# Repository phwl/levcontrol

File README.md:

# Optical levitation project

 * **pylqg_project**
   - A good starting point is [pylqg_project/notebooks/levitated_optomechanics_LQG_1d.ipynb](https://github.com/phwl/levcontrol/blob/main/pylqg_project/notebooks/levitated_optomechanics_LQG_1d.ipynb) which is a tutorial explaining the idea in 1D.
   - The high-level DAC board design is in [pylqg_project/notebooks/AD3552R_four_channel_DAC_circuit_design_tutorial.ipynb](https://github.com/phwl/levcontrol/blob/main/pylqg_project/notebooks/AD3552R_four_channel_DAC_circuit_design_tutorial.ipynb) and the details in [ad3552r_dac/docs/AD3552R_DAC_Mezzanine_Design_Manual.docx](https://github.com/phwl/levcontrol/blob/main/ad3552r_dac/docs/AD3552R_DAC_Mezzanine_Design_Manual.docx)
   - A notebook to reproduce the paper is here [pylqg_project/notebooks/pylqg_tutorial.ipynb](https://github.com/phwl/levcontrol/blob/main/pylqg_project/notebooks/pylqg_tutorial.ipynb)
 * **LQGcontroller** - repository containing the code and artifacts accompanying the article: "FPGA-based LQG controller and hardware-in-the-loop simulator implementation for nanomechanical systems"

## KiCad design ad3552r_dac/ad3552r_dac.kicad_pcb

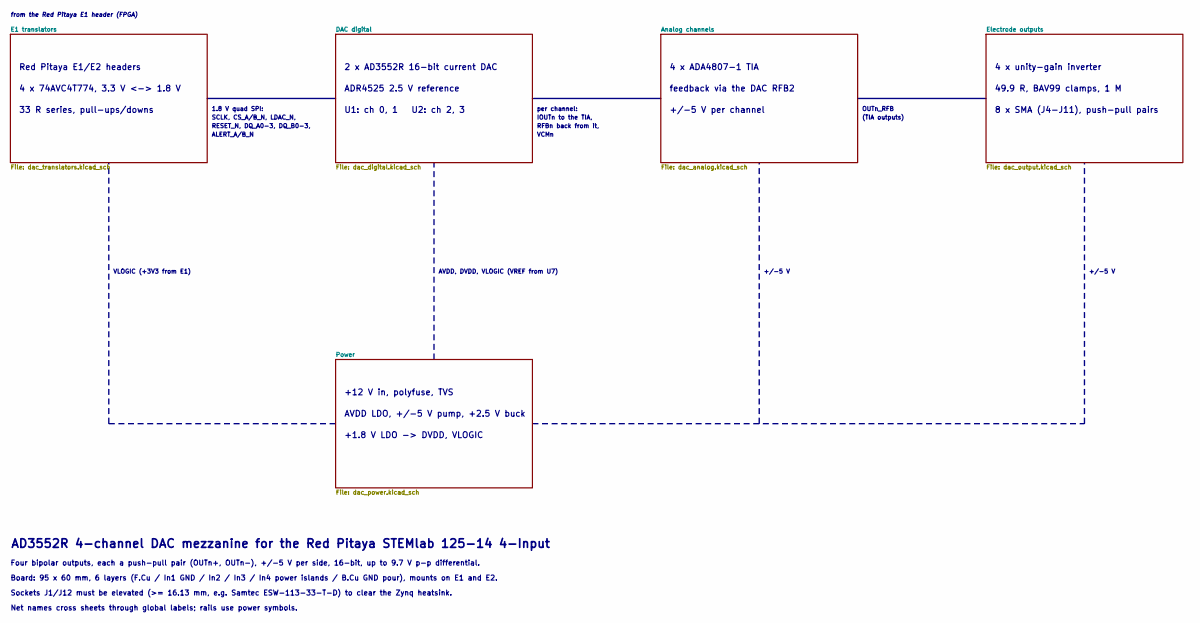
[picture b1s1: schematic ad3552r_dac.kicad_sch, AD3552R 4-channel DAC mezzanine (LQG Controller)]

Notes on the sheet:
Red Pitaya E1/E2 headers
+1.8 V LDO -> DVDD, VLOGIC
Board: 95 x 60 mm, 6 layers (F.Cu / In1 GND / In2 / In3 / In4 power islands / B.Cu GND pour), mounts on E1 and E2.
+12 V in, polyfuse, TVS
RESET_N, DQ_A0-3, DQ_B0-3,
2 x AD3552R 16-bit current DAC
U1: ch 0, 1 U2: ch 2, 3
4 x unity-gain inverter
ALERT_A/B_N
AVDD LDO, +/-5 V pump, +2.5 V buck
AVDD, DVDD, VLOGIC (VREF from U7)
+/-5 V
OUTn_RFB
+/-5 V per channel
per channel:
(TIA outputs)
from the Red Pitaya E1 header (FPGA)
RFBn back from it,
IOUTn to the TIA,
4 x ADA4807-1 TIA
4 x 74AVC4T774, 3.3 V <-> 1.8 V
Sockets J1/J12 must be elevated (>= 16.13 mm, e.g. Samtec ESW-113-33-T-D) to clear the Zynq heatsink.
8 x SMA (J4-J11), push-pull pairs
33 R series, pull-ups/downs
49.9 R, BAV99 clamps, 1 M
SCLK, CS_A/B_N, LDAC_N,
VLOGIC (+3V3 from E1)
1.8 V quad SPI:
AD3552R 4-channel DAC mezzanine for the Red Pitaya STEMlab 125-14 4-Input
Four bipolar outputs, each a push-pull pair (OUTn+, OUTn-), +/-5 V per side, 16-bit, up to 9.7 V p-p differential.
ADR4525 2.5 V reference
VCMn
Net names cross sheets through global labels; rails use power symbols.
feedback via the DAC RFB2

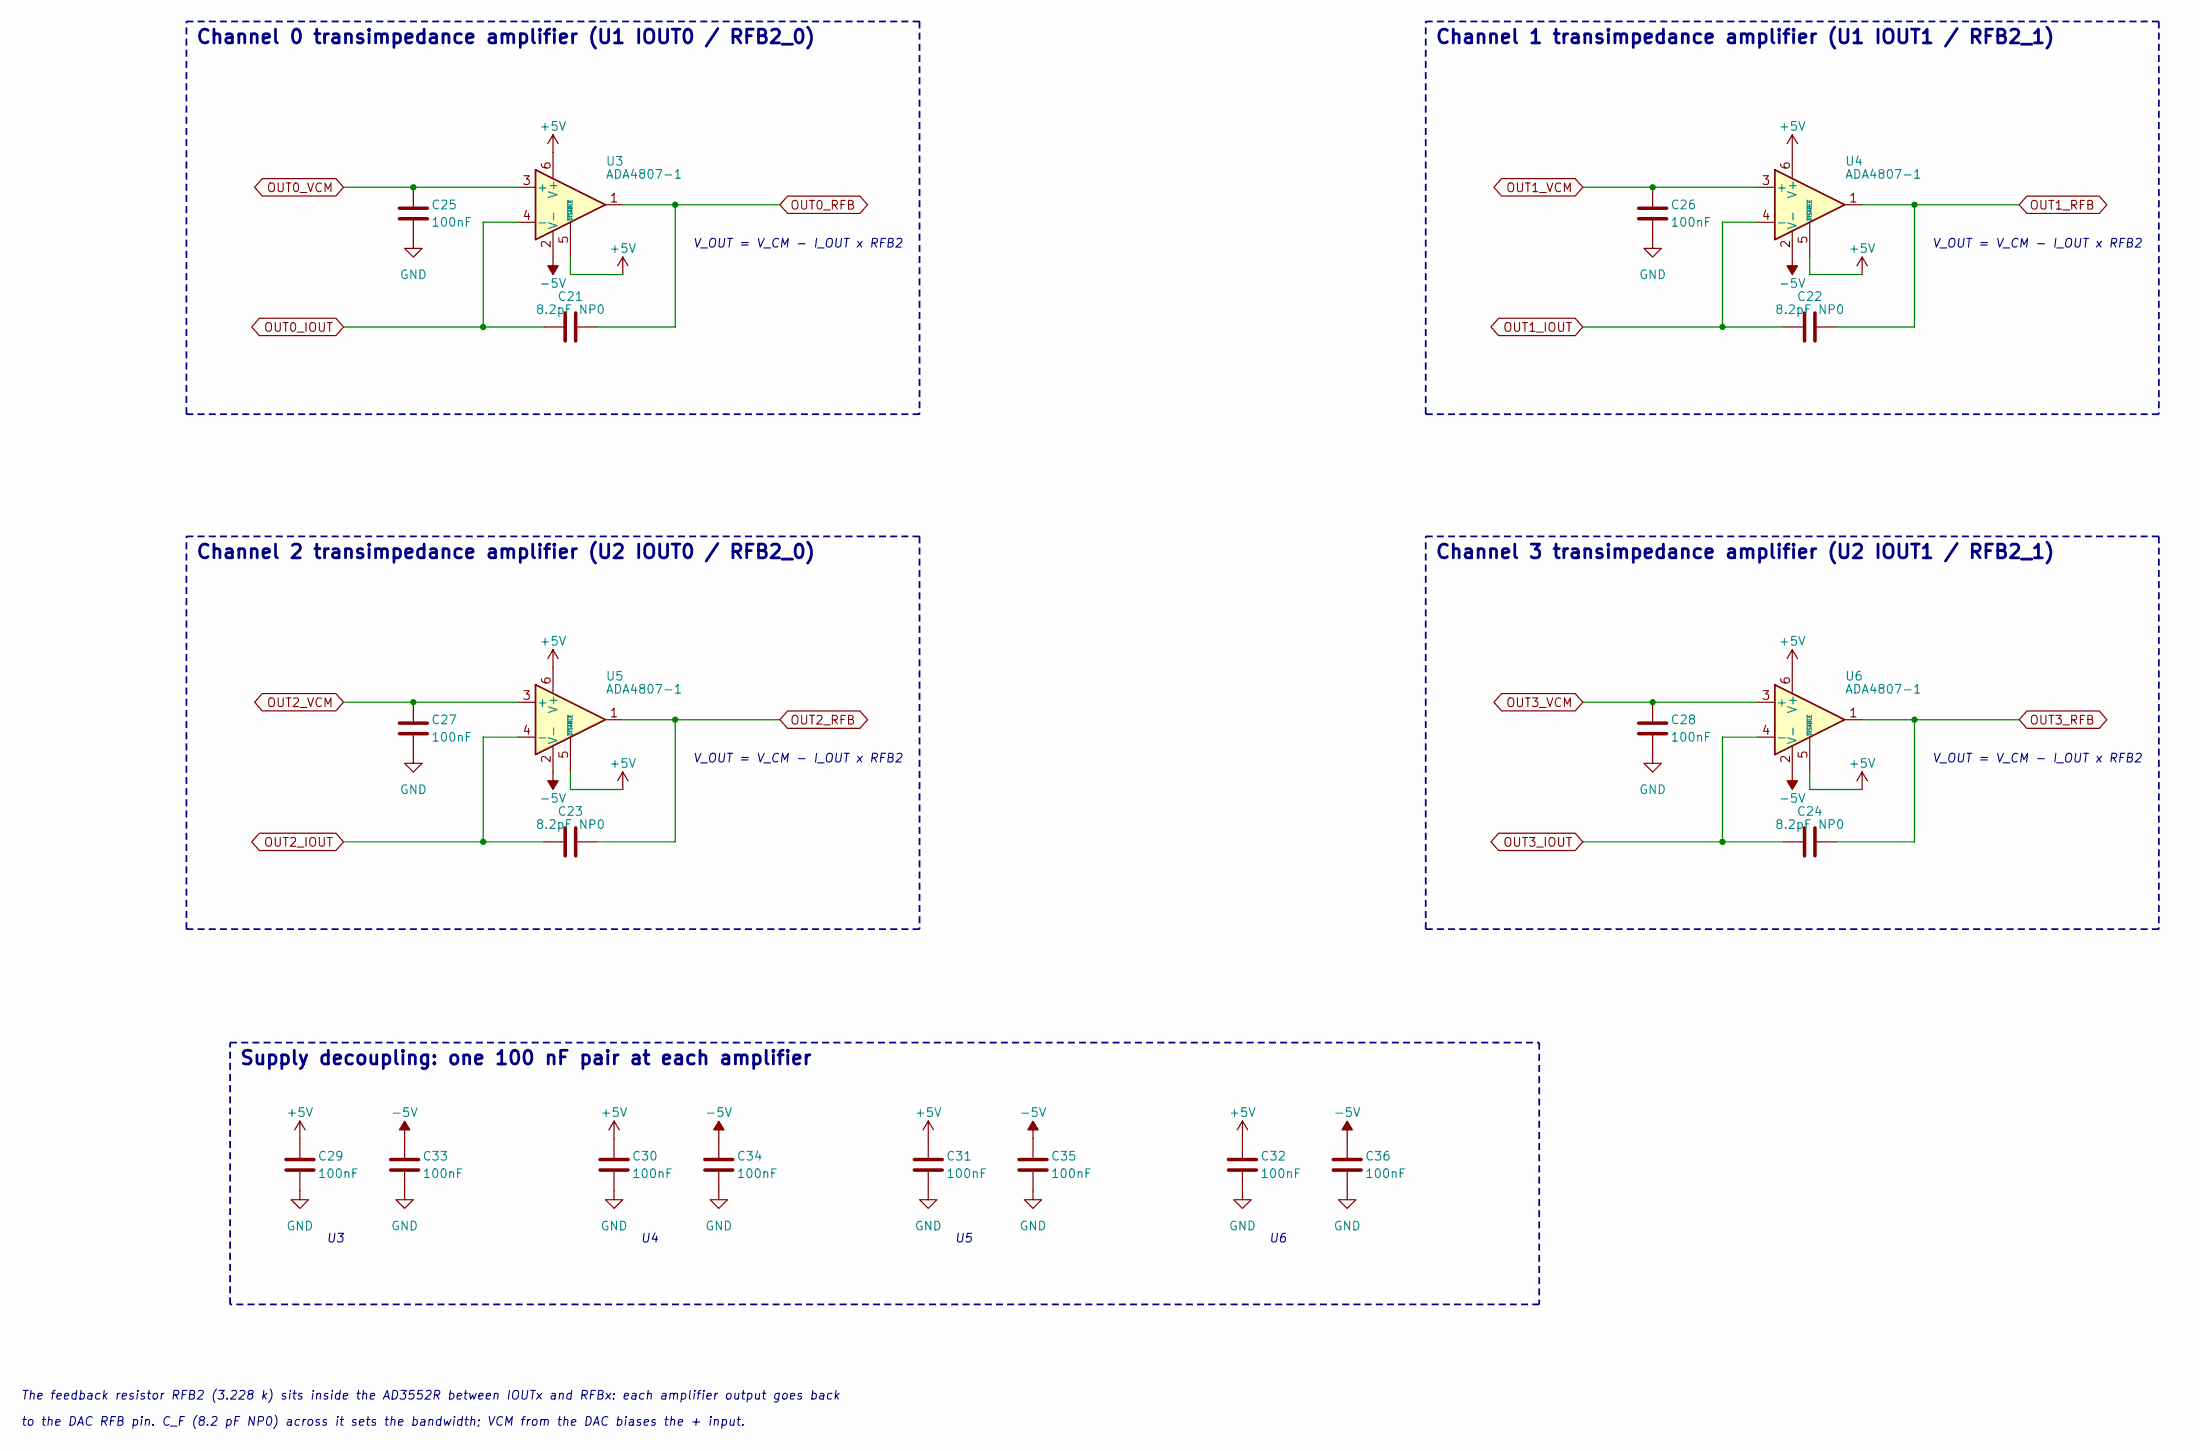
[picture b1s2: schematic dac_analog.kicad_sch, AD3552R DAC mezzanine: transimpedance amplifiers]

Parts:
C21, C22, C23, C24: 8.2pF NP0; C_0402_1005Metric; MPN 0402CG8R2C500NT; LCSC C1579
C25, C26, C27, C28, C29, C30, C31, C32, C33, C34, C35, C36: 100nF; C_0402_1005Metric; MPN CL05B104KO5NNNC; LCSC C1525
U3, U4, U5, U6: ADA4807-1; SOT-23-6; MPN ADA4807-1ARJZ-R7; LCSC C2058411

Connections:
+5V: C29.1, C30.1, C31.1, C32.1, U3.5 (~DISABLE), U3.6 (V+), U4.5 (~DISABLE), U4.6 (V+), U5.5 (~DISABLE), U5.6 (V+), U6.5 (~DISABLE), U6.6 (V+); also elsewhere on the board
-5V: C33.2, C34.2, C35.2, C36.2, U3.2 (V-), U4.2 (V-), U5.2 (V-), U6.2 (V-); also elsewhere on the board
GND: C25.2, C26.2, C27.2, C28.2, C29.2, C30.2, C31.2, C32.2, C33.1, C34.1, C35.1, C36.1; also elsewhere on the board
OUT0_IOUT: C21.1, U3.4 (-); also elsewhere on the board
OUT0_RFB: C21.2, U3.1; also elsewhere on the board
OUT0_VCM: C25.1, U3.3 (+); also elsewhere on the board
OUT1_IOUT: C22.1, U4.4 (-); also elsewhere on the board
OUT1_RFB: C22.2, U4.1; also elsewhere on the board
OUT1_VCM: C26.1, U4.3 (+); also elsewhere on the board
OUT2_IOUT: C23.1, U5.4 (-); also elsewhere on the board
OUT2_RFB: C23.2, U5.1; also elsewhere on the board
OUT2_VCM: C27.1, U5.3 (+); also elsewhere on the board
OUT3_IOUT: C24.1, U6.4 (-); also elsewhere on the board
OUT3_RFB: C24.2, U6.1; also elsewhere on the board
OUT3_VCM: C28.1, U6.3 (+); also elsewhere on the board

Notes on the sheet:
Supply decoupling: one 100 nF pair at each amplifier
Channel 3 transimpedance amplifier (U2 IOUT1 / RFB2_1)
V_OUT = V_CM - I_OUT x RFB2
Channel 0 transimpedance amplifier (U1 IOUT0 / RFB2_0)
Channel 2 transimpedance amplifier (U2 IOUT0 / RFB2_0)
Channel 1 transimpedance amplifier (U1 IOUT1 / RFB2_1)
to the DAC RFB pin. C_F (8.2 pF NP0) across it sets the bandwidth; VCM from the DAC biases the + input.
The feedback resistor RFB2 (3.228 k) sits inside the AD3552R between IOUTx and RFBx: each amplifier output goes back

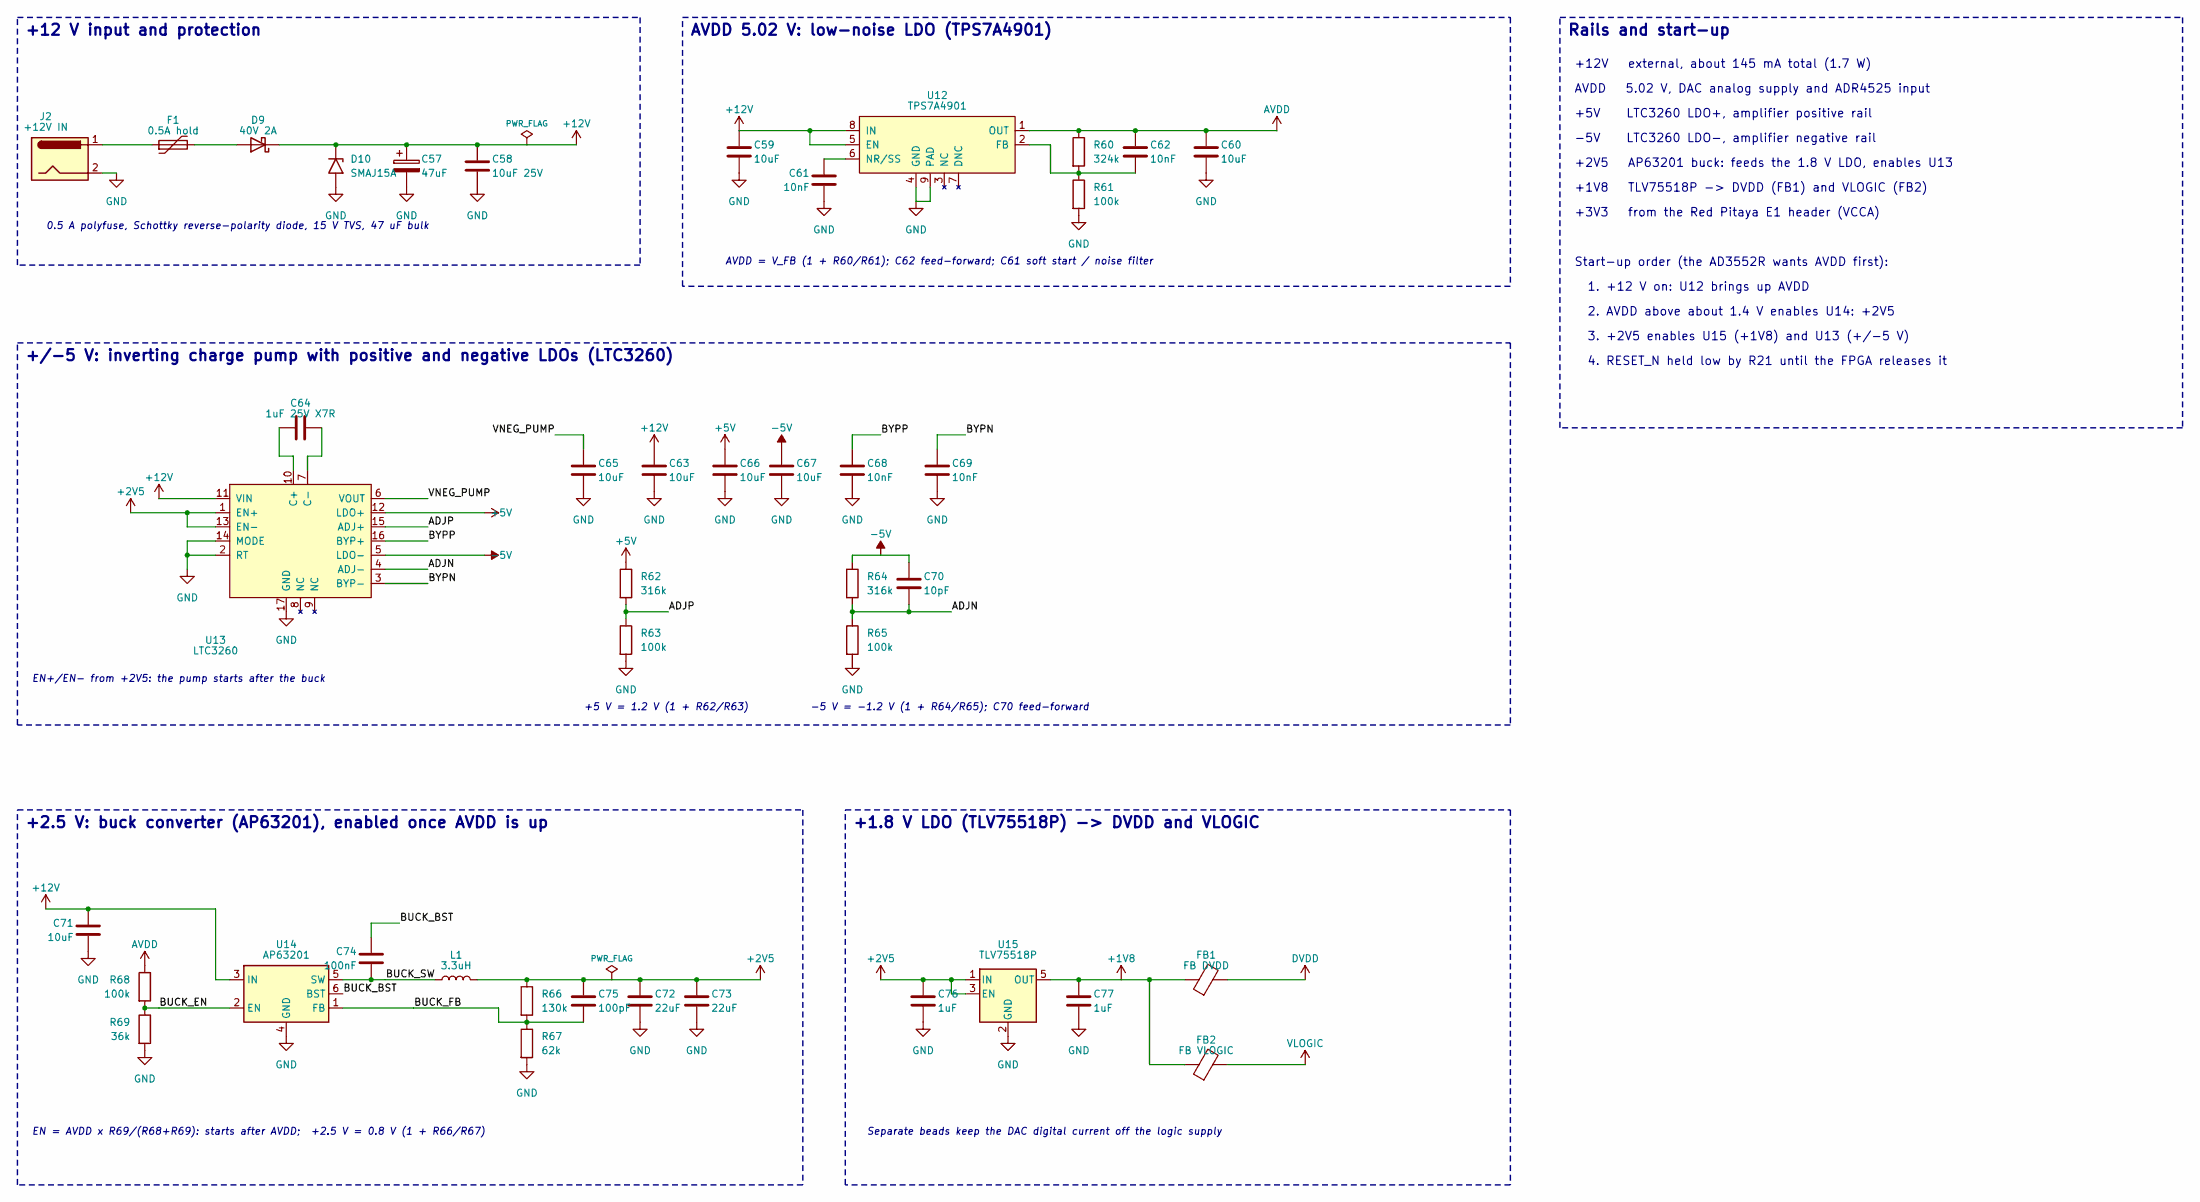
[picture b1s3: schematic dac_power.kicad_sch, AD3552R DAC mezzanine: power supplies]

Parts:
C57: 47uF; CP_Elec_6.3x5.4; MPN FVH025ADA470M0654; LCSC C7469965
C58: 10uF 25V; C_0805_2012Metric; MPN CGA0805X7R106K250MT; LCSC C6119932
C59, C60, C63, C65, C66, C67, C71: 10uF; C_0805_2012Metric; MPN CGA0805X7R106K250MT; LCSC C6119932
C61, C62, C68, C69: 10nF; C_0402_1005Metric; MPN CL05B103KB5NNNC; LCSC C15195
C64: 1uF 25V X7R; C_0603_1608Metric; MPN CC0603KRX7R8BB105; LCSC C106858
C70: 10pF; C_0402_1005Metric; MPN 0402CG100J500NT; LCSC C1545
C72, C73: 22uF; C_0805_2012Metric; MPN CL21A226MAQNNNE; LCSC C45783
C74: 100nF; C_0402_1005Metric; MPN CL05B104KO5NNNC; LCSC C1525
C75: 100pF; C_0402_1005Metric; MPN 0402CG101J500NT; LCSC C1546
C76, C77: 1uF; C_0402_1005Metric; MPN CL05A105KA5NQNC; LCSC C52923
D9: 40V 2A; D_SMA; MPN SS24; LCSC C50645
D10: SMAJ15A; D_SMA; MPN SMAJ15A/TR13; LCSC C86819
F1: 0.5A hold; Fuse_1206_3216Metric; MPN SMD1206P050TF/24; LCSC C492011
FB1: FB DVDD; L_0603_1608Metric; MPN BLM18PG221SN1D; LCSC C80165
FB2: FB VLOGIC; L_0603_1608Metric; MPN BLM18PG221SN1D; LCSC C80165
J2: +12V IN; BarrelJack_Horizontal; MPN PJ-102AH; LCSC C3096093
L1: 3.3uH; L_Taiyo-Yuden_NR-50xx; MPN SWPA5040S3R3NT; LCSC C305173
R60: 324k; R_0402_1005Metric; MPN 0402WGF3243TCE; LCSC C113480
R61, R63, R65, R68: 100k; R_0402_1005Metric; MPN 0402WGF1003TCE; LCSC C25741
R62, R64: 316k; R_0402_1005Metric; MPN 0402WGF3163TCE; LCSC C25777
R66: 130k; R_0402_1005Metric; MPN 0402WGF1303TCE; LCSC C52929
R67: 62k; R_0402_1005Metric; MPN 0402WGF6202TCE; LCSC C37825
R69: 36k; R_0402_1005Metric; MPN 0402WGF3602TCE; LCSC C43676
U12: TPS7A4901; HVSSOP-8-1EP_3x3mm_P0.65mm_EP1.57x1.89mm; MPN TPS7A4901DGNR; LCSC C16430
U13: LTC3260; MSOP-16-1EP_3x4mm_P0.5mm_EP1.65x2.85mm; MPN LTC3260EMSE#TRPBF; LCSC C684387
U14: AP63201; TSOT-23-6; MPN AP63201WU-7; LCSC C2071044
U15: TLV75518P; SOT-23-5; MPN TLV75518PDBVR; LCSC C2877863

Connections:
+1V8: C77.1, FB1.1, FB2.1, U15.5 (OUT)
+2V5: C72.1, C73.1, C75.1, C76.1, L1.2, R66.1, U13.1 (EN+), U13.13 (EN-), U15.1 (IN), U15.3 (EN)
+5V: C66.1, R62.1, U13.12 (LDO+); also elsewhere on the board
+12V: C57.1, C58.1, C59.1, C63.1, C71.1, D9.1 (K), D10.1 (A1), U12.5 (EN), U12.8 (IN), U13.11 (VIN), U14.3 (IN)
-5V: C67.1, C70.1, R64.1, U13.5 (LDO-); also elsewhere on the board
/Power/ADJN: C70.2, R64.2, R65.1, U13.4 (ADJ-)
/Power/ADJP: R62.2, R63.1, U13.15 (ADJ+)
/Power/BUCK_BST: C74.2, U14.6 (BST)
/Power/BUCK_EN: R68.2, R69.1, U14.2 (EN)
/Power/BUCK_FB: C75.2, R66.2, R67.1, U14.1 (FB)
/Power/BUCK_SW: C74.1, L1.1, U14.5 (SW)
/Power/BYPN: C69.1, U13.3 (BYP-)
/Power/BYPP: C68.1, U13.16 (BYP+)
/Power/VNEG_PUMP: C65.1, U13.6 (VOUT)
AVDD: C60.1, C62.1, R60.1, R68.1, U12.1 (OUT); also elsewhere on the board
DVDD: FB1.2; also elsewhere on the board
GND: C57.2, C58.2, C59.2, C60.2, C61.2, C63.2, C65.2, C66.2, C67.2, C68.2, C69.2, C71.2, C72.2, C73.2, C76.2, C77.2, D10.2 (A2), J2.2, R61.2, R63.2, R65.2, R67.2, R69.2, U12.4 (GND), U12.9 (PAD), U13.2 (RT), U13.14 (MODE), U13.17 (GND), U14.4 (GND), U15.2 (GND); also elsewhere on the board
unnamed: D9.2 (A), F1.2
unnamed: F1.1, J2.1
unnamed: C62.2, R60.2, R61.1, U12.2 (FB)
unnamed: C61.1, U12.6 (NR/SS)
unnamed: C64.1, U13.10 (C+)
unnamed: C64.2, U13.7 (C-)
VLOGIC: FB2.2; also elsewhere on the board

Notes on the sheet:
Start-up order (the AD3552R wants AVDD first):
3. +2V5 enables U15 (+1V8) and U13 (+/-5 V)
+5 V = 1.2 V (1 + R62/R63)
4. RESET_N held low by R21 until the FPGA releases it
+3V3 from the Red Pitaya E1 header (VCCA)
-5 V = -1.2 V (1 + R64/R65); C70 feed-forward
-5V LTC3260 LDO-, amplifier negative rail
+2V5 AP63201 buck: feeds the 1.8 V LDO, enables U13
+12V external, about 145 mA total (1.7 W)
+12 V input and protection
AVDD = V_FB (1 + R60/R61); C62 feed-forward; C61 soft start / noise filter
+5V LTC3260 LDO+, amplifier positive rail
AVDD 5.02 V, DAC analog supply and ADR4525 input
Rails and start-up
+1.8 V LDO (TLV75518P) -> DVDD and VLOGIC
1. +12 V on: U12 brings up AVDD
EN = AVDD x R69/(R68+R69): starts after AVDD; +2.5 V = 0.8 V (1 + R66/R67)
+1V8 TLV75518P -> DVDD (FB1) and VLOGIC (FB2)
EN+/EN- from +2V5: the pump starts after the buck
Separate beads keep the DAC digital current off the logic supply
0.5 A polyfuse, Schottky reverse-polarity diode, 15 V TVS, 47 uF bulk
+/-5 V: inverting charge pump with positive and negative LDOs (LTC3260)
+2.5 V: buck converter (AP63201), enabled once AVDD is up
2. AVDD above about 1.4 V enables U14: +2V5
AVDD 5.02 V: low-noise LDO (TPS7A4901)

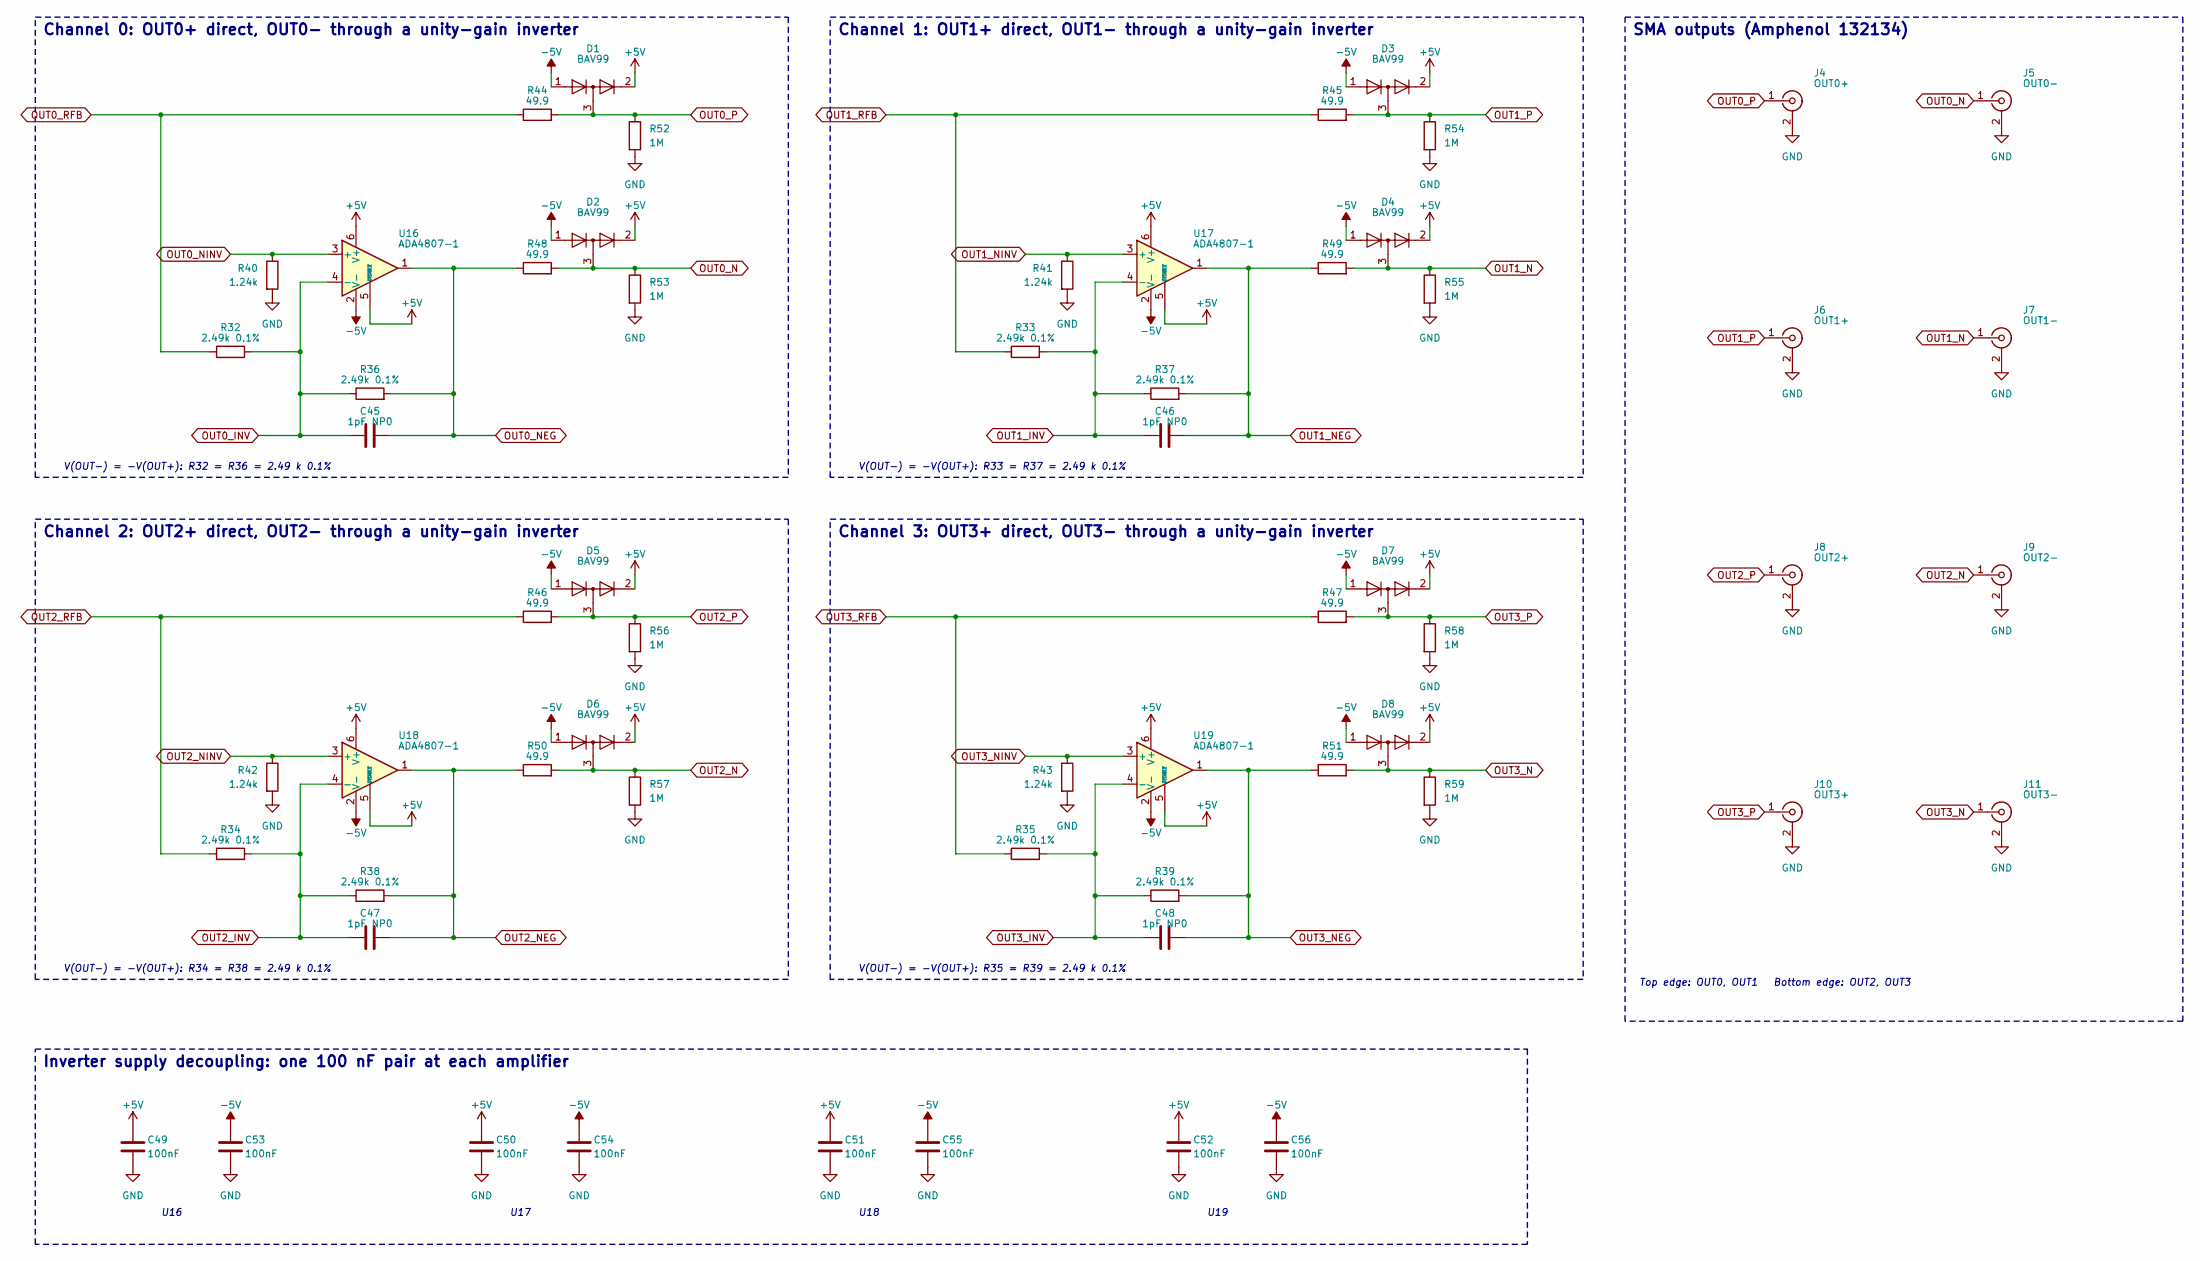
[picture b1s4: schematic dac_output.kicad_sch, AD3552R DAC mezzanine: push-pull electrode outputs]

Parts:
C45, C46, C47, C48: 1pF NP0; C_0402_1005Metric; MPN 0402CG1R0C500NT; LCSC C1550
C49, C50, C51, C52, C53, C54, C55, C56: 100nF; C_0402_1005Metric; MPN CL05B104KO5NNNC; LCSC C1525
D1, D2, D3, D4, D5, D6, D7, D8: BAV99; SOT-23; MPN BAV99,215; LCSC C2500
J4: OUT0+; SMA_Amphenol_132134_Vertical; MPN 132134; LCSC C3174425
J5: OUT0-; SMA_Amphenol_132134_Vertical; MPN 132134; LCSC C3174425
J6: OUT1+; SMA_Amphenol_132134_Vertical; MPN 132134; LCSC C3174425
J7: OUT1-; SMA_Amphenol_132134_Vertical; MPN 132134; LCSC C3174425
J8: OUT2+; SMA_Amphenol_132134_Vertical; MPN 132134; LCSC C3174425
J9: OUT2-; SMA_Amphenol_132134_Vertical; MPN 132134; LCSC C3174425
J10: OUT3+; SMA_Amphenol_132134_Vertical; MPN 132134; LCSC C3174425
J11: OUT3-; SMA_Amphenol_132134_Vertical; MPN 132134; LCSC C3174425
R32, R33, R34, R35, R36, R37, R38, R39: 2.49k 0.1%; R_0603_1608Metric; MPN RT0603BRD072K49L; LCSC C861299
R40, R41, R42, R43: 1.24k; R_0402_1005Metric; MPN 0402WGF1241TCE; LCSC C25864
R44, R45, R46, R47, R48, R49, R50, R51: 49.9; R_0402_1005Metric; MPN 0402WGF499JTCE; LCSC C25120
R52, R53, R54, R55, R56, R57, R58, R59: 1M; R_0402_1005Metric; MPN 0402WGF1004TCE; LCSC C26083
U16, U17, U18, U19: ADA4807-1; SOT-23-6; MPN ADA4807-1ARJZ-R7; LCSC C2058411

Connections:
+5V: C49.1, C50.1, C51.1, C52.1, D1.2 (A), D2.2 (A), D3.2 (A), D4.2 (A), D5.2 (A), D6.2 (A), D7.2 (A), D8.2 (A), U16.5 (~DISABLE), U16.6 (V+), U17.5 (~DISABLE), U17.6 (V+), U18.5 (~DISABLE), U18.6 (V+), U19.5 (~DISABLE), U19.6 (V+); also elsewhere on the board
-5V: C53.2, C54.2, C55.2, C56.2, D1.1 (K), D2.1 (K), D3.1 (K), D4.1 (K), D5.1 (K), D6.1 (K), D7.1 (K), D8.1 (K), U16.2 (V-), U17.2 (V-), U18.2 (V-), U19.2 (V-); also elsewhere on the board
GND: C49.2, C50.2, C51.2, C52.2, C53.1, C54.1, C55.1, C56.1, J4.2 (Ext), J5.2 (Ext), J6.2 (Ext), J7.2 (Ext), J8.2 (Ext), J9.2 (Ext), J10.2 (Ext), J11.2 (Ext), R40.2, R41.2, R42.2, R43.2, R52.2, R53.2, R54.2, R55.2, R56.2, R57.2, R58.2, R59.2; also elsewhere on the board
OUT0_INV: C45.1, R32.2, R36.1, U16.4 (-)
OUT0_N: D2.3 (K), J5.1 (In), R48.2, R53.1
OUT0_NEG: C45.2, R36.2, R48.1, U16.1
OUT0_NINV: R40.1, U16.3 (+)
OUT0_P: D1.3 (K), J4.1 (In), R44.2, R52.1
OUT0_RFB: R32.1, R44.1; also elsewhere on the board
OUT1_INV: C46.1, R33.2, R37.1, U17.4 (-)
OUT1_N: D4.3 (K), J7.1 (In), R49.2, R55.1
OUT1_NEG: C46.2, R37.2, R49.1, U17.1
OUT1_NINV: R41.1, U17.3 (+)
OUT1_P: D3.3 (K), J6.1 (In), R45.2, R54.1
OUT1_RFB: R33.1, R45.1; also elsewhere on the board
OUT2_INV: C47.1, R34.2, R38.1, U18.4 (-)
OUT2_N: D6.3 (K), J9.1 (In), R50.2, R57.1
OUT2_NEG: C47.2, R38.2, R50.1, U18.1
OUT2_NINV: R42.1, U18.3 (+)
OUT2_P: D5.3 (K), J8.1 (In), R46.2, R56.1
OUT2_RFB: R34.1, R46.1; also elsewhere on the board
OUT3_INV: C48.1, R35.2, R39.1, U19.4 (-)
OUT3_N: D8.3 (K), J11.1 (In), R51.2, R59.1
OUT3_NEG: C48.2, R39.2, R51.1, U19.1
OUT3_NINV: R43.1, U19.3 (+)
OUT3_P: D7.3 (K), J10.1 (In), R47.2, R58.1
OUT3_RFB: R35.1, R47.1; also elsewhere on the board

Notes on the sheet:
Channel 2: OUT2+ direct, OUT2- through a unity-gain inverter
Channel 1: OUT1+ direct, OUT1- through a unity-gain inverter
Top edge: OUT0, OUT1 Bottom edge: OUT2, OUT3
U17
U16
Inverter supply decoupling: one 100 nF pair at each amplifier
SMA outputs (Amphenol 132134)
U19
V(OUT-) = -V(OUT+): R34 = R38 = 2.49 k 0.1%
V(OUT-) = -V(OUT+): R33 = R37 = 2.49 k 0.1%
Channel 3: OUT3+ direct, OUT3- through a unity-gain inverter
U18
Channel 0: OUT0+ direct, OUT0- through a unity-gain inverter
V(OUT-) = -V(OUT+): R35 = R39 = 2.49 k 0.1%
V(OUT-) = -V(OUT+): R32 = R36 = 2.49 k 0.1%

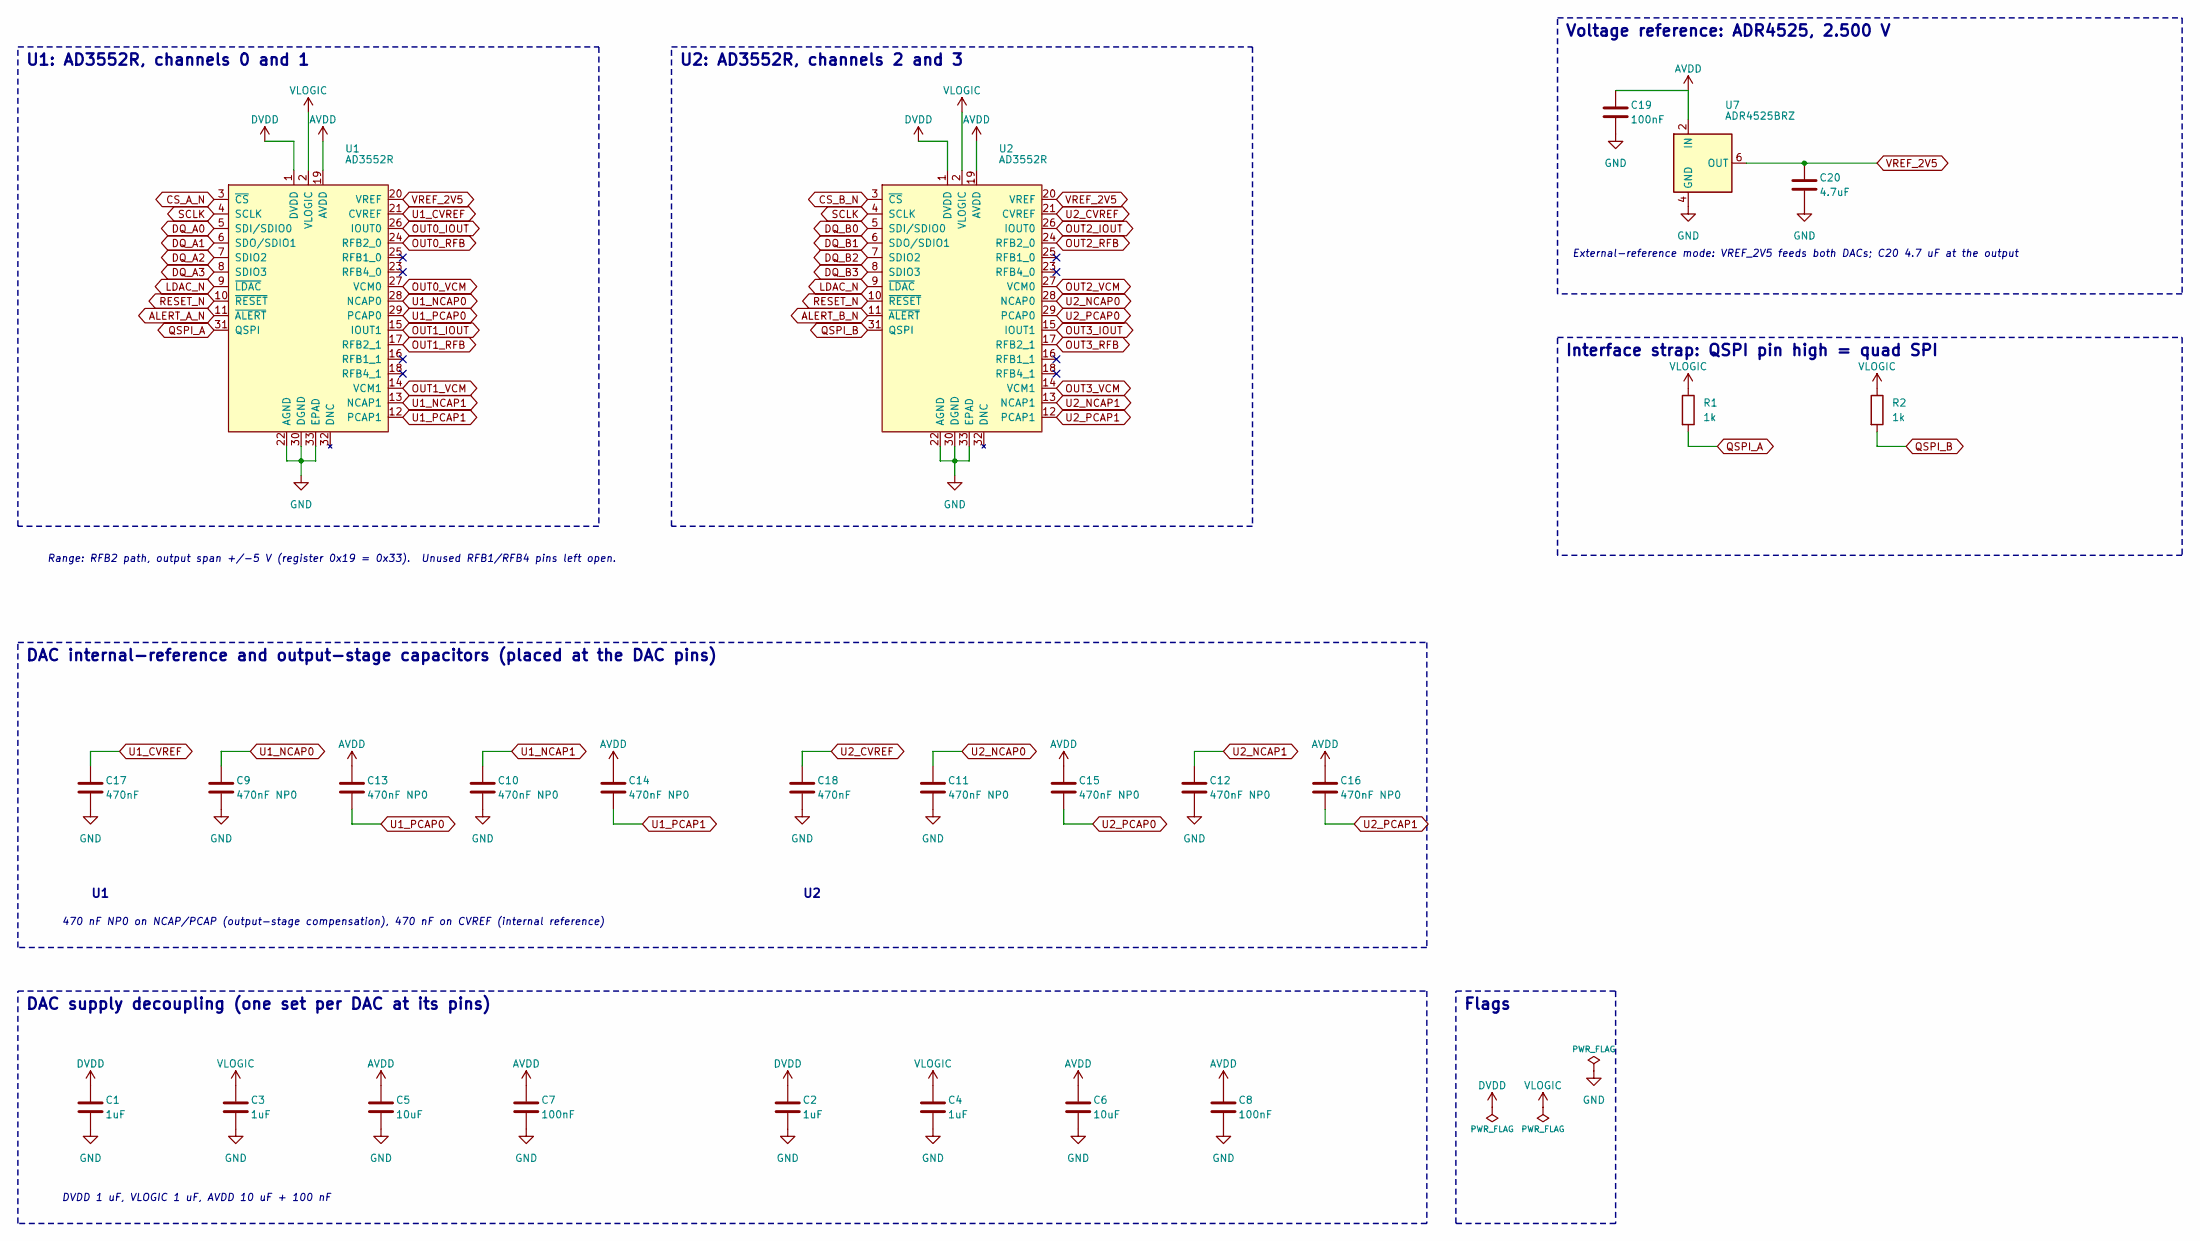
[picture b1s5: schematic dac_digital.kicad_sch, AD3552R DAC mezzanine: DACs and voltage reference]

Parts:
C1, C2, C3, C4: 1uF; C_0402_1005Metric
C5, C6: 10uF; C_0805_2012Metric
C7, C8, C19: 100nF; C_0402_1005Metric
C9, C10, C11, C12, C13, C14, C15, C16: 470nF NP0; C_1206_3216Metric
C17, C18: 470nF; C_0603_1608Metric
C20: 4.7uF; C_0603_1608Metric
R1, R2: 1k; R_0402_1005Metric
U1, U2: AD3552R; LFCSP-32-1EP_5x5mm_P0.5mm_EP3.1x3.1mm
U7: ADR4525BRZ; SOIC-8_3.9x4.9mm_P1.27mm

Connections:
ALERT_A_N: U1.11 (~ALERT); also elsewhere on the board
ALERT_B_N: U2.11 (~ALERT); also elsewhere on the board
AVDD: C5.1, C6.1, C7.1, C8.1, C13.2, C14.2, C15.2, C16.2, C19.1, U1.19 (AVDD), U2.19 (AVDD), U7.2 (IN); also elsewhere on the board
CS_A_N: U1.3 (~CS); also elsewhere on the board
CS_B_N: U2.3 (~CS); also elsewhere on the board
DQ_A0: U1.5 (SDI/SDIO0); also elsewhere on the board
DQ_A1: U1.6 (SDO/SDIO1); also elsewhere on the board
DQ_A2: U1.7 (SDIO2); also elsewhere on the board
DQ_A3: U1.8 (SDIO3); also elsewhere on the board
DQ_B0: U2.5 (SDI/SDIO0); also elsewhere on the board
DQ_B1: U2.6 (SDO/SDIO1); also elsewhere on the board
DQ_B2: U2.7 (SDIO2); also elsewhere on the board
DQ_B3: U2.8 (SDIO3); also elsewhere on the board
DVDD: C1.1, C2.1, U1.1 (DVDD), U2.1 (DVDD); also elsewhere on the board
GND: C1.2, C2.2, C3.2, C4.2, C5.2, C6.2, C7.2, C8.2, C9.2, C10.2, C11.2, C12.2, C17.2, C18.2, C19.2, C20.2, U1.22 (AGND), U1.30 (DGND), U1.33 (EPAD), U2.22 (AGND), U2.30 (DGND), U2.33 (EPAD), U7.4 (GND); also elsewhere on the board
LDAC_N: U1.9 (~LDAC), U2.9 (~LDAC); also elsewhere on the board
OUT0_IOUT: U1.26 (IOUT0); also elsewhere on the board
OUT0_RFB: U1.24 (RFB2_0); also elsewhere on the board
OUT0_VCM: U1.27 (VCM0); also elsewhere on the board
OUT1_IOUT: U1.15 (IOUT1); also elsewhere on the board
OUT1_RFB: U1.17 (RFB2_1); also elsewhere on the board
OUT1_VCM: U1.14 (VCM1); also elsewhere on the board
OUT2_IOUT: U2.26 (IOUT0); also elsewhere on the board
OUT2_RFB: U2.24 (RFB2_0); also elsewhere on the board
OUT2_VCM: U2.27 (VCM0); also elsewhere on the board
OUT3_IOUT: U2.15 (IOUT1); also elsewhere on the board
OUT3_RFB: U2.17 (RFB2_1); also elsewhere on the board
OUT3_VCM: U2.14 (VCM1); also elsewhere on the board
QSPI_A: R1.2, U1.31 (QSPI)
QSPI_B: R2.2, U2.31 (QSPI)
RESET_N: U1.10 (~RESET), U2.10 (~RESET); also elsewhere on the board
SCLK: U1.4 (SCLK), U2.4 (SCLK); also elsewhere on the board
U1_CVREF: C17.1, U1.21 (CVREF)
U1_NCAP0: C9.1, U1.28 (NCAP0)
U1_NCAP1: C10.1, U1.13 (NCAP1)
U1_PCAP0: C13.1, U1.29 (PCAP0)
U1_PCAP1: C14.1, U1.12 (PCAP1)
U2_CVREF: C18.1, U2.21 (CVREF)
U2_NCAP0: C11.1, U2.28 (NCAP0)
U2_NCAP1: C12.1, U2.13 (NCAP1)
U2_PCAP0: C15.1, U2.29 (PCAP0)
U2_PCAP1: C16.1, U2.12 (PCAP1)
VLOGIC: C3.1, C4.1, R1.1, R2.1, U1.2 (VLOGIC), U2.2 (VLOGIC); also elsewhere on the board
VREF_2V5: C20.1, U1.20 (VREF), U2.20 (VREF), U7.6 (OUT)

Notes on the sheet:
U1: AD3552R, channels 0 and 1
DVDD 1 uF, VLOGIC 1 uF, AVDD 10 uF + 100 nF
Interface strap: QSPI pin high = quad SPI
DAC internal-reference and output-stage capacitors (placed at the DAC pins)
Range: RFB2 path, output span +/-5 V (register 0x19 = 0x33). Unused RFB1/RFB4 pins left open.
Voltage reference: ADR4525, 2.500 V
Flags
U2: AD3552R, channels 2 and 3
External-reference mode: VREF_2V5 feeds both DACs; C20 4.7 uF at the output
470 nF NP0 on NCAP/PCAP (output-stage compensation), 470 nF on CVREF (internal reference)
DAC supply decoupling (one set per DAC at its pins)
